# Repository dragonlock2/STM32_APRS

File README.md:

# STM32 APRS

APRS modulation and demodulation with a UI. Made for STM32L433.

https://matthewtran.dev/2021/01/stm32-aprs/

Potentially reusable modules (.c/.h) in Core/:
* BitFIFO/IntFIFO - FIFO queue implemented with a ring buffer
* SSD1306 - I2C driver for SSD1306 OLED w/ compact font
* Keyboard - ASCII keyboard using T9 button layout
* AFSK - High speed AFSK modulation and demodulation to and from bit streams
* APRS - High speed APRS packet generation and decoding to and from bit streams
* APRSGUI - TUI implementation for displaying and configuring APRS packets

## How to Use

### iPython

ipython/aprs.ipynb is a Python implementation of the APRS encoding and decoding algorithms written for easy conversion to C.

### KiCad

The PCB design files for the hardware are located in kicad/.

### STM32CubeIDE

APRSTest.ioc is a STM32CubeMX configuration file and was used to generate the project starter code in STM32CubeIDE. Everything in Core/ should be copied over to the generated Core/ folder, overwriting as necessary.

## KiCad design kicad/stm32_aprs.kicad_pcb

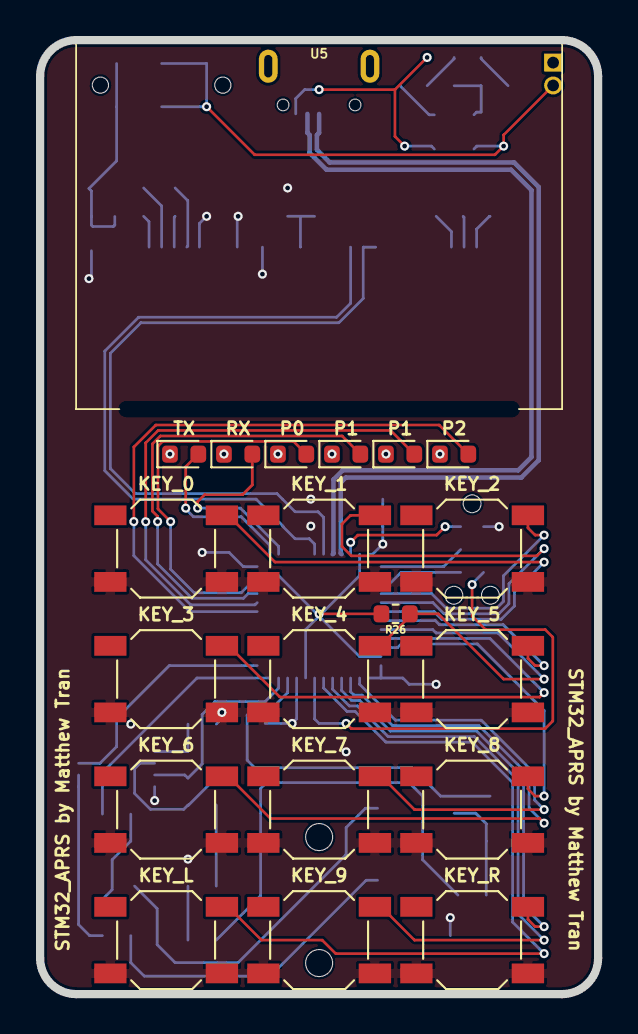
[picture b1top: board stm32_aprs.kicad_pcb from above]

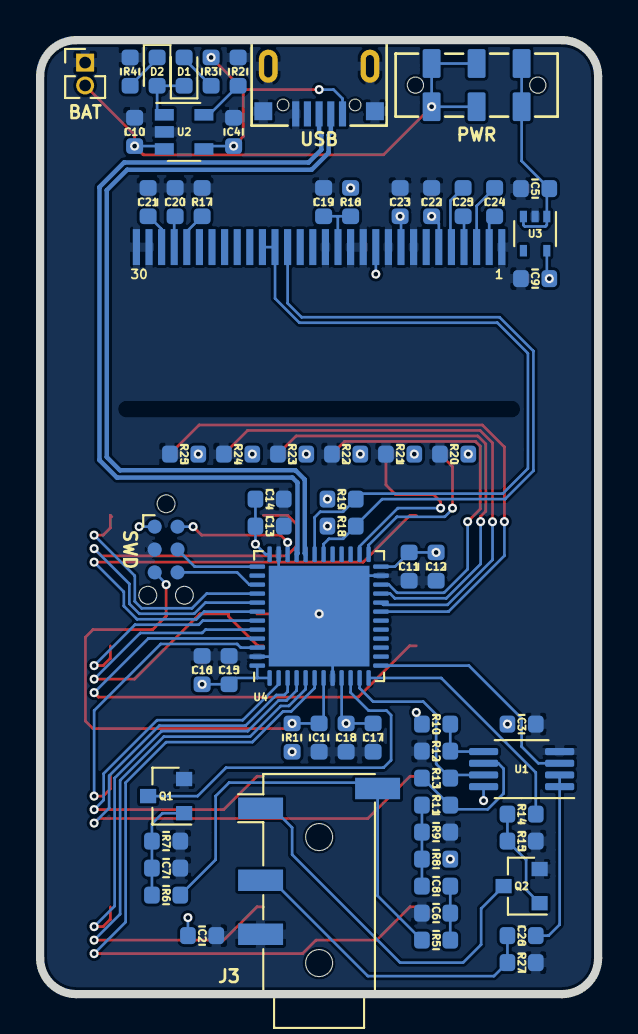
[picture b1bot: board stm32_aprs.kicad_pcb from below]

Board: 2 copper layers, 31.0 x 53.0 mm, 85 parts (65 on the bottom side), 63 nets.

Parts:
BAT: BAT; PinHeader_1x02_P1.27mm_Vertical
C1, C3, C6, C11, C13, C15, C17, C19: 100n; C_0603_1608Metric
C2, C4, C7, C10, C26: 10u; C_0603_1608Metric
C5, C8, C9, C12, C14, C16, C18, C20, C21, C22, C23, C24, C25: 1u; C_0603_1608Metric
D1: CHRG; LED_0603_1608Metric
D2: FULL; LED_0603_1608Metric
J3: Baofeng; Jack_3.5mm_PJ320D_Horizontal
KEY_0: KEY_0; SW_SPST_SKQG_WithoutStem
KEY_1: KEY_1; SW_SPST_SKQG_WithoutStem
KEY_2: KEY_2; SW_SPST_SKQG_WithoutStem
KEY_3: KEY_3; SW_SPST_SKQG_WithoutStem
KEY_4: KEY_4; SW_SPST_SKQG_WithoutStem
KEY_5: KEY_5; SW_SPST_SKQG_WithoutStem
KEY_6: KEY_6; SW_SPST_SKQG_WithoutStem
KEY_7: KEY_7; SW_SPST_SKQG_WithoutStem
KEY_8: KEY_8; SW_SPST_SKQG_WithoutStem
KEY_9: KEY_9; SW_SPST_SKQG_WithoutStem
KEY_L: KEY_L; SW_SPST_SKQG_WithoutStem
KEY_R: KEY_R; SW_SPST_SKQG_WithoutStem
P0: LED0; LED_0603_1608Metric
P1: LED2; LED_0603_1608Metric
P1#2: LED1; LED_0603_1608Metric
P2: LED3; LED_0603_1608Metric
PWR: PWR_SW; JS202011JAQN
Q1, Q2: DMG2302U; SOT-23
R1, R6, R10, R11, R12, R15, R16, R26: 10k; R_0603_1608Metric
R2, R3, R4, R18, R19, R27: 2.2k; R_0603_1608Metric
R5: 470; R_0603_1608Metric
R7: 22k; R_0603_1608Metric
R8, R9, R20, R21, R22, R23, R24, R25: 1k; R_0603_1608Metric
R13: 47k; R_0603_1608Metric
R14: 22; R_0603_1608Metric
R17: 470k; R_0603_1608Metric
RX: RX; LED_0603_1608Metric
SWD: SWD; Tag-Connect_TC2030-IDC-NL_2x03_P1.27mm_Vertical
TX: TX; LED_0603_1608Metric
U1: MCP6L02x-xMS; MSOP-8_3x3mm_P0.65mm
U2: MCP73831-2-OT; SOT-23-5
U3: MIC5365-3.3YC5; SOT-353_SC-70-5
U4: STM32L433CCUx; QFN-48-1EP_7x7mm_P0.5mm_EP5.6x5.6mm
U5: SSD1306
USB: USB_B_Micro; U254-051N-4BH83-F1B

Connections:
+3V3: C2.2, C3.2, C9.1, C11.1, C12.1, C13.1, C14.1, C15.1, C16.1, C17.1, C18.1, C22.1, C23.1, KEY_0.2, KEY_1.2, KEY_2.2, KEY_3.2, KEY_4.2, KEY_5.2, KEY_6.2, KEY_7.2, KEY_8.2, KEY_9.2, KEY_L.2, KEY_R.2, R1.1, R8.1, R10.2, R16.1, R18.1, R19.1, SWD.1, U1.8, U3.5, U4.1, U4.9, U4.24, U4.36, U4.48, U5.6, U5.9, U5.11
+3V8: BAT.2, C10.1, PWR.2, PWR.3, PWR.5, PWR.6, U2.3
+5V: C4.2, R3.1, U2.4, USB.1
/ADC_IN: R13.1, U1.7, U4.11
/AUDIO_IN: J3.S, R5.2, R6.2
/AUDIO_OUT: C26.1, J3.R1, R27.1
/BOOT0_KEY_4: KEY_4.1, R26.1, U4.44
/DAC_OUT: U1.3, U4.13
/KEY_0: KEY_0.1, U4.42
/KEY_1: KEY_1.1, U4.41
/KEY_2: KEY_2.1, U4.40
/KEY_3: KEY_3.1, U4.45
/KEY_5: KEY_5.1, U4.43
/KEY_6: KEY_6.1, U4.3
/KEY_7: KEY_7.1, U4.2
/KEY_8: KEY_8.1, U4.46
/KEY_9: KEY_9.1, U4.5
/KEY_L: KEY_L.1, U4.6
/KEY_R: KEY_R.1, U4.4
/LED_0: P0.2, U4.22
/LED_1: P1#2.2, U4.21
/LED_2: P1.2, U4.20
/LED_3: P2.2, U4.19
/NRST: C1.1, R1.2, SWD.5, U4.7
/PTT: J3.T, Q2.3
/RX_DET: Q1.3, U4.10
/RX_LED: RX.2, U4.26
/SCL: R18.2, U4.30, U5.18
/SDA: R19.2, U4.31, U5.19, U5.20
/SWCLK: SWD.4, U4.37
/SWDIO: SWD.2, U4.34
/SWO: SWD.6, U4.39
/TX_LED: TX.2, U4.25
/TX_PTT: R14.2, U4.12
/USB_N: U4.32, USB.2
/USB_P: U4.33, USB.3
GND: BAT.1, C1.2, C2.1, C3.1, C4.1, C5.1, C6.2, C7.2, C9.2, C10.2, C11.2, C12.2, C13.2, C14.2, C15.2, C16.2, C17.2, C18.2, C19.2, C20.2, C21.2, C22.2, C23.2, J3.R2, Q1.2, Q2.2, R2.2, R4.1, R7.2, R9.2, R12.1, R15.2, R17.2, R20.1, R21.1, R22.1, R23.1, R24.1, R25.1, R26.2, R27.2, SWD.3, U1.4, U2.2, U3.2, U4.8, U4.23, U4.35, U4.47, U4.49, U5.1, U5.8, U5.10, U5.12, U5.13, U5.15, U5.29, U5.30, USB.5, USB.6
unnamed: C5.2, PWR.1, PWR.4, U3.1, U3.3
unnamed: C6.1, C8.2, R5.1
unnamed: C7.1, Q1.1, R6.1, R7.1
unnamed: C8.1, R8.2, R9.1, R11.2
unnamed: C19.1, R16.2, U5.14
unnamed: C20.1, U5.27
unnamed: C21.1, U5.28
unnamed: C24.1, U5.2
unnamed: C24.2, U5.3
unnamed: C25.1, U5.4
unnamed: C25.2, U5.5
unnamed: C26.2, U1.1, U1.2
unnamed: D1.1, D2.2, U2.1
unnamed: D1.2, R3.2
unnamed: D2.1, R4.2
unnamed: R20.2, TX.1
unnamed: R21.2, RX.1
unnamed: P0.1, R22.2
unnamed: P1#2.1, R23.2
unnamed: P1.1, R24.2
unnamed: P2.1, R25.2
unnamed: Q2.1, R14.1, R15.1
unnamed: R2.1, U2.5
unnamed: R10.1, R12.2, U1.5
unnamed: R11.1, R13.2, U1.6
unnamed: R17.1, U5.26

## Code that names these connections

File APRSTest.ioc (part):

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Mcu.Name=STM32L433C(B-C)Ux
Mcu.Package=UFQFPN48
Mcu.UserName=STM32L433CCUx
PA0.GPIOParameters=GPIO_PuPd,GPIO_Label
PA0.GPIO_Label=RX_DET
PA0.GPIO_PuPd=GPIO_PULLUP
PA0.Signal=GPIO_Input
PA1.Signal=ADCx_IN6
PA10.Mode=I2C
PA10.Signal=I2C1_SDA
PA11.Mode=Device
PA11.Signal=USB_DM
PA12.Mode=Device
PA12.Signal=USB_DP
PA13\ (JTMS-SWDIO).Mode=Trace_Asynchronous_SW
PA13\ (JTMS-SWDIO).Signal=SYS_JTMS-SWDIO
PA14\ (JTCK-SWCLK).Mode=Trace_Asynchronous_SW
PA14\ (JTCK-SWCLK).Signal=SYS_JTCK-SWCLK
PA2.GPIOParameters=GPIO_Speed,GPIO_Label
PA2.GPIO_Label=TX_PTT
PA2.GPIO_Speed=GPIO_SPEED_FREQ_VERY_HIGH
PA2.Signal=GPIO_Output
PA3.Mode=Follower-DAC_OUT1-INP
PA3.Signal=OPAMP1_VOUT
PA9.Mode=I2C
PA9.Signal=I2C1_SCL
PB1.GPIOParameters=GPIO_Speed,GPIO_Label
PB1.GPIO_Label=LED_3
PB1.GPIO_Speed=GPIO_SPEED_FREQ_VERY_HIGH
PB1.Signal=GPIO_Output
PB10.GPIOParameters=GPIO_Speed,GPIO_Label
PB10.GPIO_Label=LED_1
PB10.GPIO_Speed=GPIO_SPEED_FREQ_VERY_HIGH
PB10.Signal=GPIO_Output
PB11.GPIOParameters=GPIO_Speed,GPIO_Label
PB11.GPIO_Label=LED_0
PB11.GPIO_Speed=GPIO_SPEED_FREQ_VERY_HIGH
PB11.Signal=GPIO_Output
PB12.GPIOParameters=GPIO_Speed,GPIO_Label
PB12.GPIO_Label=TX_LED
PB12.GPIO_Speed=GPIO_SPEED_FREQ_VERY_HIGH
PB12.Signal=GPIO_Output
PB13.GPIOParameters=GPIO_Speed,GPIO_Label
PB13.GPIO_Label=RX_LED
PB13.GPIO_Speed=GPIO_SPEED_FREQ_VERY_HIGH
PB13.Signal=GPIO_Output
PB2.GPIOParameters=GPIO_Speed,GPIO_Label
PB2.GPIO_Label=LED_2
PB2.GPIO_Speed=GPIO_SPEED_FREQ_VERY_HIGH
PB2.Signal=GPIO_Output
PB3\ (JTDO-TRACESWO).Mode=Trace_Asynchronous_SW
PB3\ (JTDO-TRACESWO).Signal=SYS_JTDO-SWO
PB4\ (NJTRST).GPIOParameters=GPIO_PuPd,GPIO_Label
PB4\ (NJTRST).GPIO_Label=KEY_2
PB4\ (NJTRST).GPIO_PuPd=GPIO_PULLDOWN
PB4\ (NJTRST).Signal=GPIO_Input
PB5.GPIOParameters=GPIO_PuPd,GPIO_Label
PB5.GPIO_Label=KEY_1
PB5.GPIO_PuPd=GPIO_PULLDOWN
PB5.Signal=GPIO_Input
PB6.GPIOParameters=GPIO_PuPd,GPIO_Label
PB6.GPIO_Label=KEY_0
PB6.GPIO_PuPd=GPIO_PULLDOWN
PB6.Signal=GPIO_Input
PB7.GPIOParameters=GPIO_PuPd,GPIO_Label
PB7.GPIO_Label=KEY_5
PB7.GPIO_PuPd=GPIO_PULLDOWN
PB7.Signal=GPIO_Input
PB8.GPIOParameters=GPIO_PuPd,GPIO_Label
PB8.GPIO_Label=KEY_3
PB8.GPIO_PuPd=GPIO_PULLDOWN
PB8.Signal=GPIO_Input
PB9.GPIOParameters=GPIO_PuPd,GPIO_Label
PB9.GPIO_Label=KEY_8
PB9.GPIO_PuPd=GPIO_PULLDOWN
PB9.Signal=GPIO_Input
PC13.GPIOParameters=GPIO_PuPd,GPIO_Label
PC13.GPIO_Label=KEY_7
PC13.GPIO_PuPd=GPIO_PULLDOWN
PC13.Signal=GPIO_Input
PC14-OSC32_IN\ (PC14).GPIOParameters=GPIO_PuPd,GPIO_Label
PC14-OSC32_IN\ (PC14).GPIO_Label=KEY_6
PC14-OSC32_IN\ (PC14).GPIO_PuPd=GPIO_PULLDOWN
PC14-OSC32_IN\ (PC14).Signal=GPIO_Input
PC15-OSC32_OUT\ (PC15).GPIOParameters=GPIO_PuPd,GPIO_Label
PC15-OSC32_OUT\ (PC15).GPIO_Label=KEY_R
PC15-OSC32_OUT\ (PC15).GPIO_PuPd=GPIO_PULLDOWN
PC15-OSC32_OUT\ (PC15).Signal=GPIO_Input
PH0-OSC_IN\ (PH0).GPIOParameters=GPIO_PuPd,GPIO_Label
PH0-OSC_IN\ (PH0).GPIO_Label=KEY_9
PH0-OSC_IN\ (PH0).GPIO_PuPd=GPIO_PULLDOWN
PH0-OSC_IN\ (PH0).Signal=GPIO_Input
PH1-OSC_OUT\ (PH1).GPIOParameters=GPIO_PuPd,GPIO_Label
PH1-OSC_OUT\ (PH1).GPIO_Label=KEY_L
PH1-OSC_OUT\ (PH1).GPIO_PuPd=GPIO_PULLDOWN
PH1-OSC_OUT\ (PH1).Signal=GPIO_Input
PH3-BOOT0.GPIOParameters=GPIO_PuPd,GPIO_Label
PH3-BOOT0.GPIO_Label=KEY_4
PH3-BOOT0.GPIO_PuPd=GPIO_PULLDOWN
PH3-BOOT0.Signal=GPIO_Input
RCC.HSE_VALUE=8000000
RCC.SYSCLKFreq_VALUE=80000000
RCC.SYSCLKSource=RCC_SYSCLKSOURCE_PLLCLK
board=custom

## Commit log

2021-01-10 Added STM32CubeIDE files
2021-01-10 Create LICENSE
2021-01-10 Added iPython notebook
2021-01-10 Removed unneeded file
2021-01-10 Added kicad files
